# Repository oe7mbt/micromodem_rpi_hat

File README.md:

# micromodem_rpi_hat
Micromodem RPi-Hat 

based on the circuit from Mark, OZ7TMD / unsigned.io

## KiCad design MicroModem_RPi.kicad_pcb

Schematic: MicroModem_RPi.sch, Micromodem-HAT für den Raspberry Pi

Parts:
C1, C2: 22pF; C_1206_HandSoldering
C3: 4.7uF; C_1206_HandSoldering
C4: 100nF; C_1206_HandSoldering
C5: 1uF; C_1206_HandSoldering
D1: TX; LED_1206_HandSoldering
D2: RX; LED_1206_HandSoldering
J1: RADIO; Pin_Header_Angled_1x06_Pitch2.54mm
J2: PWR; Pin_Header_Angled_1x02_Pitch2.54mm
P1: RPi; PinSocket_2x20_P2.54mm_Vertical
P2: HFG; Pin_Header_Straight_1x02_Pitch2.54mm
Q1: 2N7000; TO-92_Inline_Wide
R1: 4K7; R_1206_HandSoldering
R2, R11: 10K; R_1206_HandSoldering
R3: 8K2; R_1206_HandSoldering
R4: 3K9; R_1206_HandSoldering
R5, R14: 2K2; R_1206_HandSoldering
R6, R9: 1K; R_1206_HandSoldering
R7, R8: 470R; R_1206_HandSoldering
R10: 270R; R_1206_HandSoldering
R12, R13: 100K; R_1206_HandSoldering
RV1: 100K; Potentiometer_Bourns_3296W_3-8Zoll_Inline_ScrewUp
RV2: 100K; Potentiometer_Trimmer_Piher_PT-10v10_Horizontal_Px10.0mm_Py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
SW1: HFG; SW_DIP_x1_W7.62mm_Slide
U1: ATmega328-PU; DIP-28_W7.62mm_LongPads
Y1: 16MHz; Crystal_HC49-U_Vertical

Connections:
+3V3: P1.1, P1.17, R12.2, U1.21 (AREF)
+5V: J2.2, P1.2, P1.4, U1.7 (VCC), U1.20 (AVCC)
A0: C5.1, R12.1, R13.2, U1.23 (PC0)
Analog_IN: C5.2, J1.1
Analog_OUT: J1.2, R9.1, R14.1, RV1.1, RV2.1
GND: C1.1, C2.1, C4.1, J1.5, J1.6, J2.1, P1.6, P1.9, P1.14, P1.20, P1.25, P1.30, P1.34, P1.39, Q1.1, R2.2, R7.2, R8.2, R9.2, R10.2, R11.1, R13.1, U1.8 (GND), U1.22 (GND)
MCU_RX: P1.8, U1.2 (PD0)
MCU_TX: R1.1, U1.3 (PD1)
MISO: P1.21, U1.18 (PB4)
MOSI: P1.19, U1.17 (PB3)
unnamed: C1.2, U1.9 (XTAL1/PB6), Y1.1
unnamed: C2.2, U1.10 (XTAL2/PB7), Y1.2
unnamed: C3.1, C4.2, R3.2, R4.2, R5.2, R6.2, R10.1
unnamed: C3.2, RV1.2, RV1.3, RV2.2, RV2.3
unnamed: D1.1, R7.1
unnamed: D1.2, U1.15 (PB1)
unnamed: D2.1, R8.1
unnamed: D2.2, U1.16 (PB2)
unnamed: P2.2, R14.2, SW1.2
unnamed: R3.1, U1.6 (PD4)
unnamed: R4.1, U1.11 (PD5)
unnamed: R5.1, U1.12 (PD6)
unnamed: R6.1, U1.13 (PD7)
PTT_PIN: J1.4, Q1.2, R11.2, U1.5 (PD3)
PTT_V+: J1.3, P2.1, Q1.3, SW1.1
RESET: P1.7, U1.1 (~RESET~/PC6)
RXD_RPI: P1.10, R1.2, R2.1
SCK: P1.23, U1.19 (PB5)

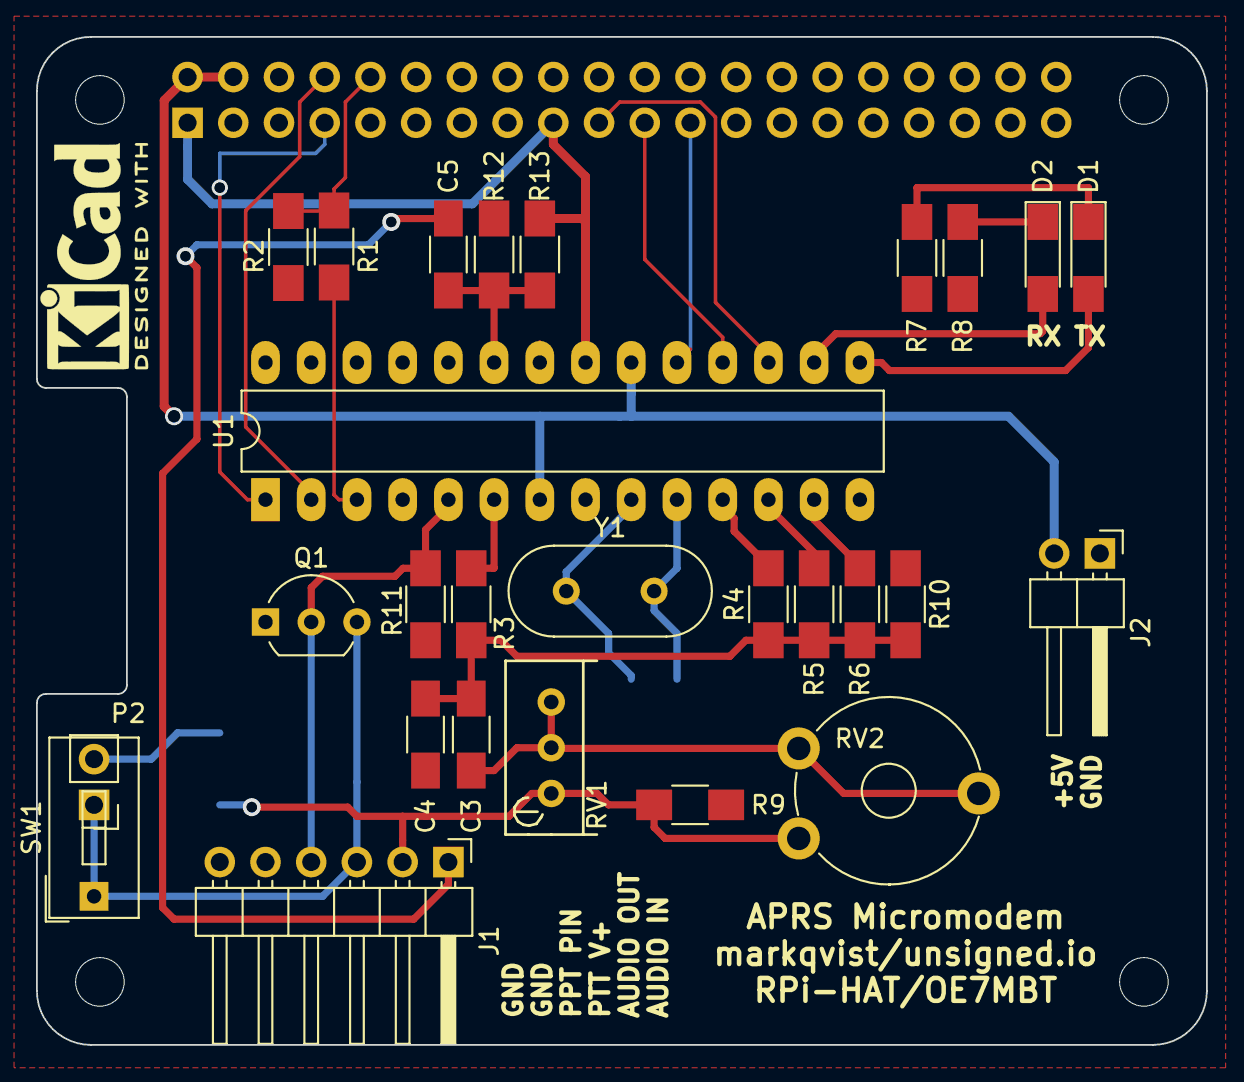
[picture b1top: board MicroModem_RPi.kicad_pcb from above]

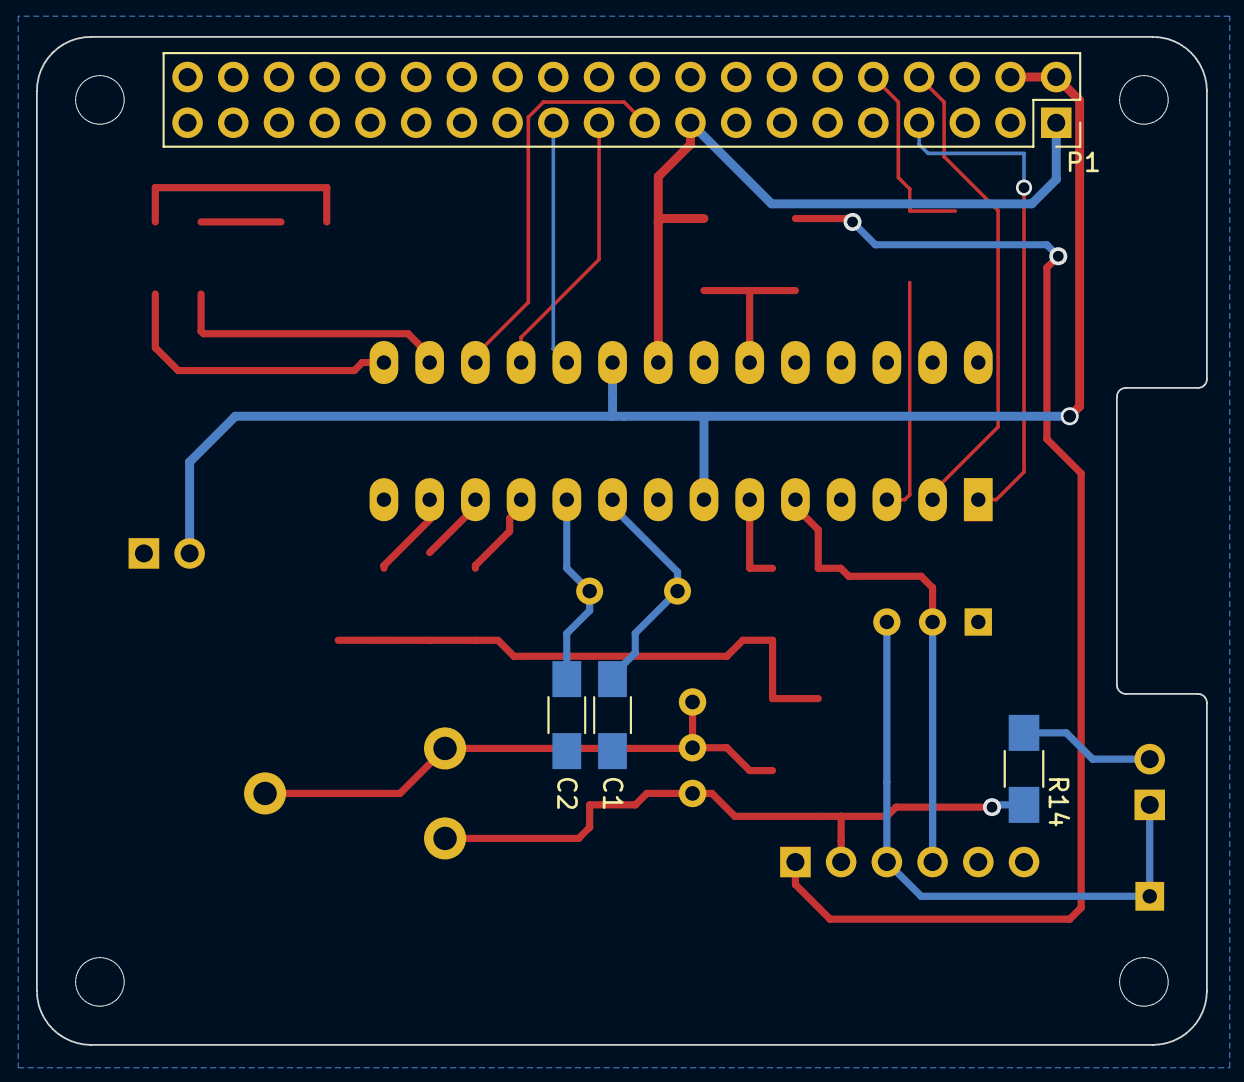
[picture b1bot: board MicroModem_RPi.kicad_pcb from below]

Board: 2 copper layers, 65.0 x 56.0 mm, 35 parts (4 on the bottom side), 28 nets.

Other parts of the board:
MK1, MK2, MK3, MK4: M2.5; MountingHole_2.7mm_M2.5
